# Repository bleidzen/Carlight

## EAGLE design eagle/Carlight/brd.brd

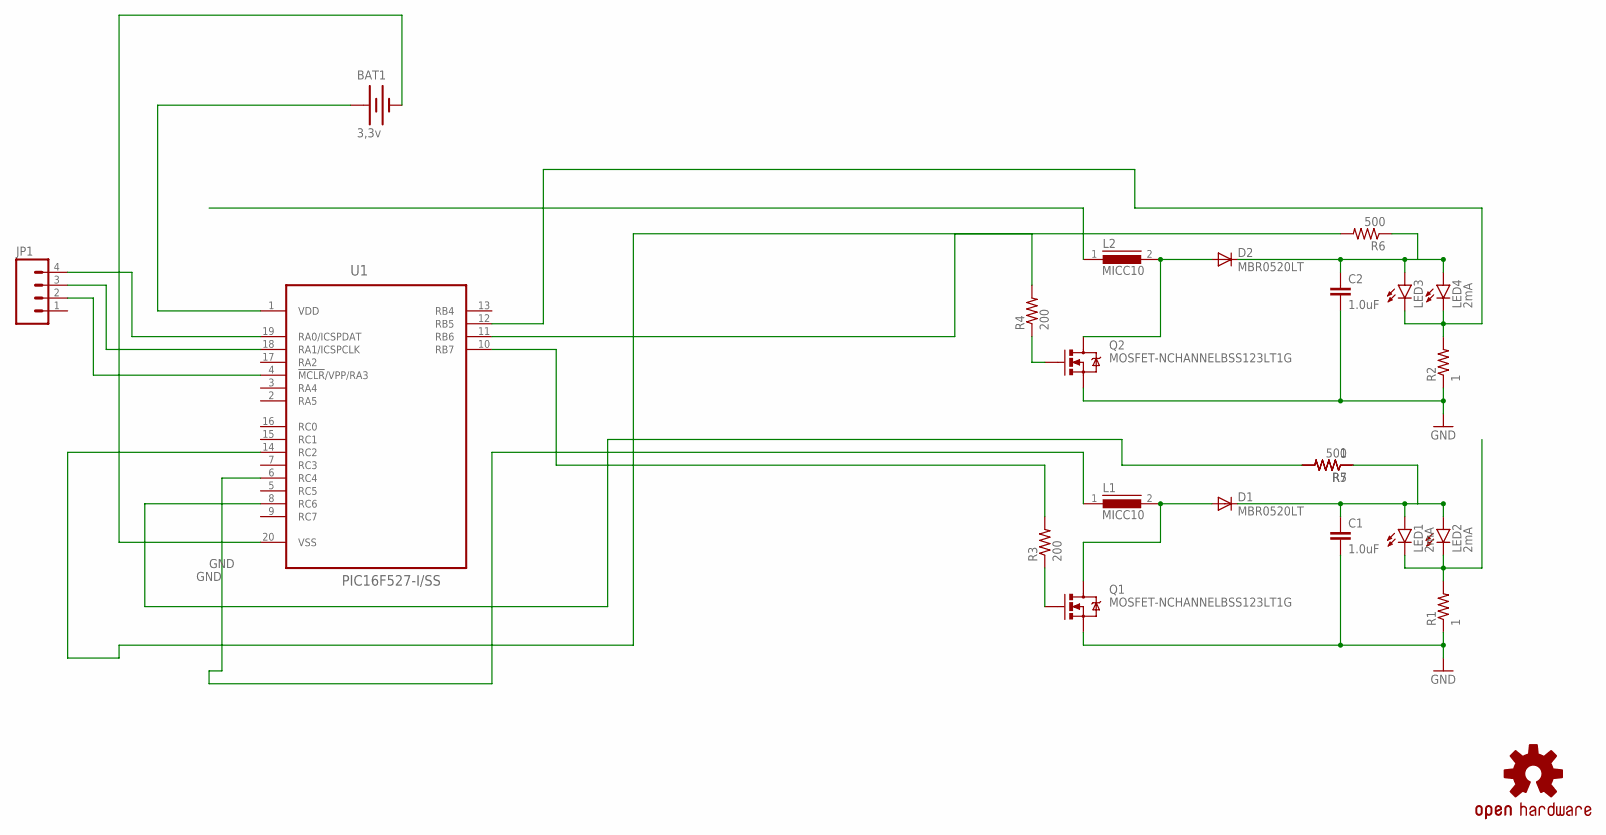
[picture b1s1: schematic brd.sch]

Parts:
BAT1: 3,3v; BATTCON_20MM
C1, C2: 1.0uF; 0805
D1, D2: MBR0520LT; SOD123
JP1: M041.27MM; 1X04-1.27MM
L1, L2: MICC10
LED1, LED2, LED4: 2mA; LED3MM-NS
LED3: LED-3MM-NO_SILK; LED3MM-NS
LOGO1: OSHW-LOGOM; OSHW-LOGO-M
Q1, Q2: MOSFET-NCHANNELBSS123LT1G; SOT23
R1, R2, R5: 1; 0805
R3, R4: 200; 0805
R6, R7: 500; 0805
U1: PIC16F527-I/SS; SOP65P780X200-20N

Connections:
GND: BAT1.2 (-), C1.2, C2.2, Q1.2 (S), Q2.2 (S), R1.1, R2.1, U1.20 (VSS)
unnamed: D1.A, L1.2, Q1.3 (D)
unnamed: R4.2, U1.11 (RB6)
unnamed: JP1.4, U1.19 (RA0/ICSPDAT)
unnamed: LED1.K (C), LED2.K (C), R1.2
unnamed: D2.A, L2.2, Q2.3 (D)
unnamed: L1.1, U1.6 (RC4)
unnamed: Q1.1 (G), R3.1
unnamed: Q2.1 (G), R4.1
unnamed: C2.1, D2.C, LED3.A, LED4.A, R6.1
unnamed: LED3.K (C), LED4.K (C), R2.2, U1.12 (RB5)
unnamed: JP1.3, U1.18 (RA1/ICSPCLK)
unnamed: R3.2, U1.10 (RB7)
unnamed: JP1.2, U1.4 (!MCLR!/VPP/RA3)
unnamed: R5.2, R7.2, U1.8 (RC6)
unnamed: C1.1, D1.C, LED1.A, LED2.A, R5.1, R7.1
unnamed: R6.2, U1.14 (RC2)
VDD: BAT1.1 (+), U1.1 (VDD)

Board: 2 copper layers, 23 parts (1 on the bottom side), 18 nets, no tracks yet.

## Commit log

2014-06-13 toy car light
    For my son
2014-06-13 Added eagle
    Eagle files added
2014-06-13 Mplabx file added
    yes it was

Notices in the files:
parts and their libraries:
SparkFun-Electromechanical: Licensing: Creative Commons ShareAlike 4.0 International - https://creativecommons.org/licenses/by-sa/4.0
